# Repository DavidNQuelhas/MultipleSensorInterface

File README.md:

# MultipleSensorInterface
Multiple Sensor Interface - versatile RTU device

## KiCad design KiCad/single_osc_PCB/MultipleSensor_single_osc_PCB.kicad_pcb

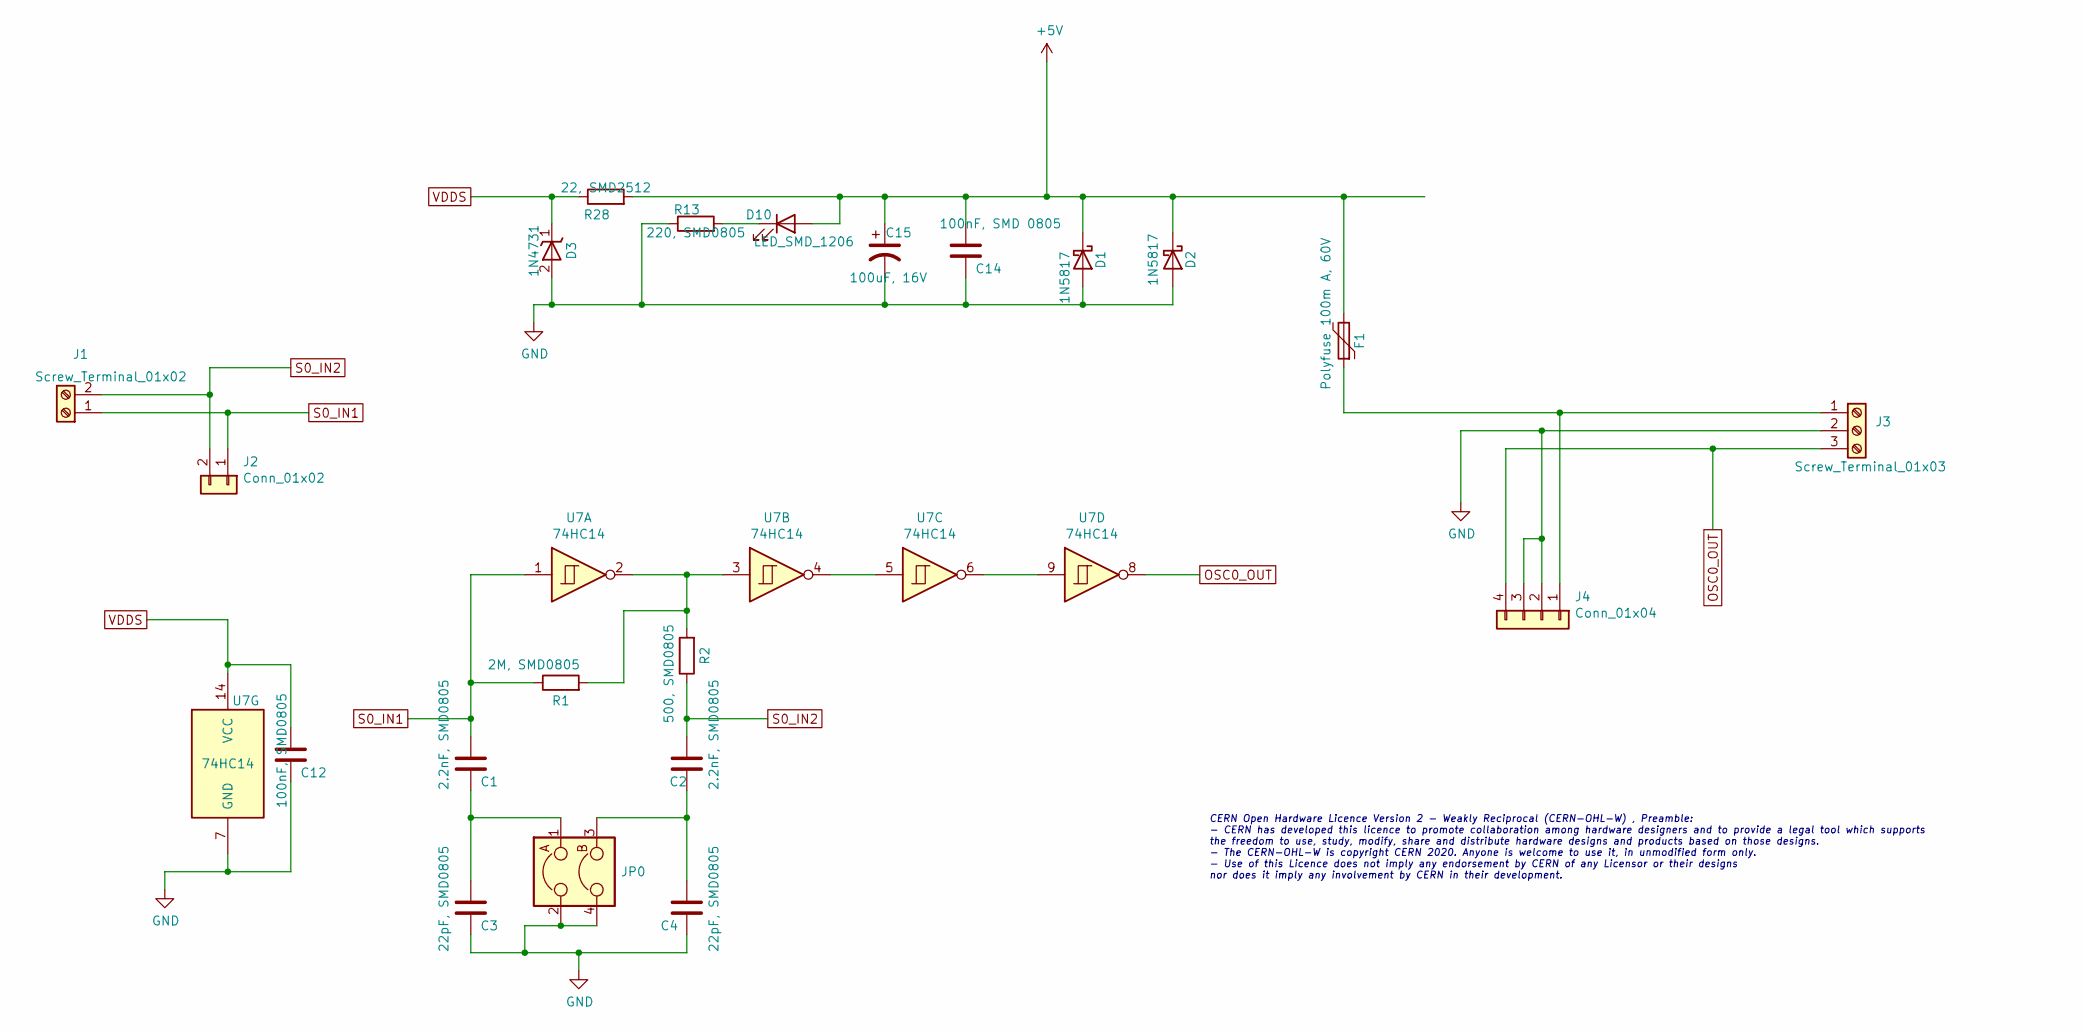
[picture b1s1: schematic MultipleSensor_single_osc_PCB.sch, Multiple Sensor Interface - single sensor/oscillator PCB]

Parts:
C1, C2: 2.2nF, SMD0805; C_0805_HandSoldering
C3, C4: 22pF, SMD0805; C_0805_HandSoldering
C12: 100nF, SMD0805; C_0805_HandSoldering
C14: 100nF, SMD 0805; C_0805_HandSoldering
C15: 100uF, 16V; CP_Radial_D5.0mm_P2.50mm
D1, D2: 1N5817; D_DO-41_SOD81_P10.16mm_Horizontal
D3: 1N4731; D_DO-41_SOD81_P10.16mm_Horizontal
D10: LED_SMD_1206; LED_1206
F1: Polyfuse 100m A, 60V; Fuse_TE5_Littlefuse-395Series
J1: Screw_Terminal_01x02; TerminalBlock_Screw_1x2_3.96mm
J2: Conn_01x02; PinHeader_1x02_P2.54mm_Vertical_HandSoldering
J3: Screw_Terminal_01x03; TerminalBlock_Screw_1x3_3.96mm
J4: Conn_01x04; PinHeader_1x04_P2.54mm_Vertical_HandSoldering
JP0: 2_jumpers_related; 2_jumpers_related_2.54mm
R1: 2M, SMD0805; R_0805_HandSoldering
R2: 500, SMD0805; R_0805_HandSoldering
R13: 220, SMD0805; R_0805_HandSoldering
R28: 22, SMD2512; R_2512_HandSoldering
U7: 74HC14; SOIC-14_3.9x8.7mm_Pitch1.27mm_HandSoldering

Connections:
+5V: C14.1, C15.1, D1.1 (K), D2.1 (K), D10.2 (A), F1.2, R28.2
GND: C3.2, C4.2, C12.2, C14.2, C15.2, D1.2 (A), D2.2 (A), D3.2 (A), J3.2, J4.2, J4.3, JP0.2, JP0.4, R13.1, U7.7 (GND)
unnamed: C1.2, C3.1, JP0.1
unnamed: C2.2, C4.1, JP0.3
unnamed: D10.1 (K), R13.2
unnamed: F1.1, J3.1, J4.1
unnamed: R1.2, R2.2, U7.2, U7.3
unnamed: U7.4, U7.5
unnamed: U7.6, U7.9
OSC0_OUT: J3.3, J4.4, U7.8
S0_IN1: C1.1, J1.1, J2.1, R1.1, U7.1
S0_IN2: C2.1, J1.2, J2.2, R2.1
VDDS: C12.1, D3.1 (K), R28.1, U7.14 (VCC)

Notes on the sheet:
CERN Open Hardware Licence Version 2 - Weakly Reciprocal (CERN-OHL-W) , Preamble: - CERN has developed this licence to promote collaboration among hardware designers and to provide a legal tool which supports the freedom to use, study, modify, share and distribute hardware designs and products base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

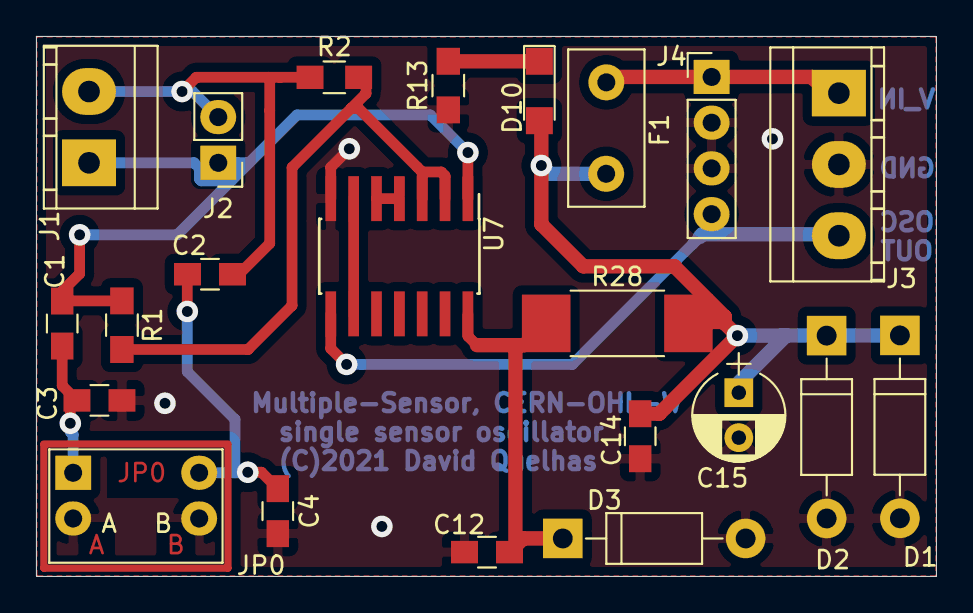
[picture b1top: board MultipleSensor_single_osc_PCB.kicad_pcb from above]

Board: 2 copper layers, 50.0 x 30.0 mm, 22 parts (0 on the bottom side), 13 nets.

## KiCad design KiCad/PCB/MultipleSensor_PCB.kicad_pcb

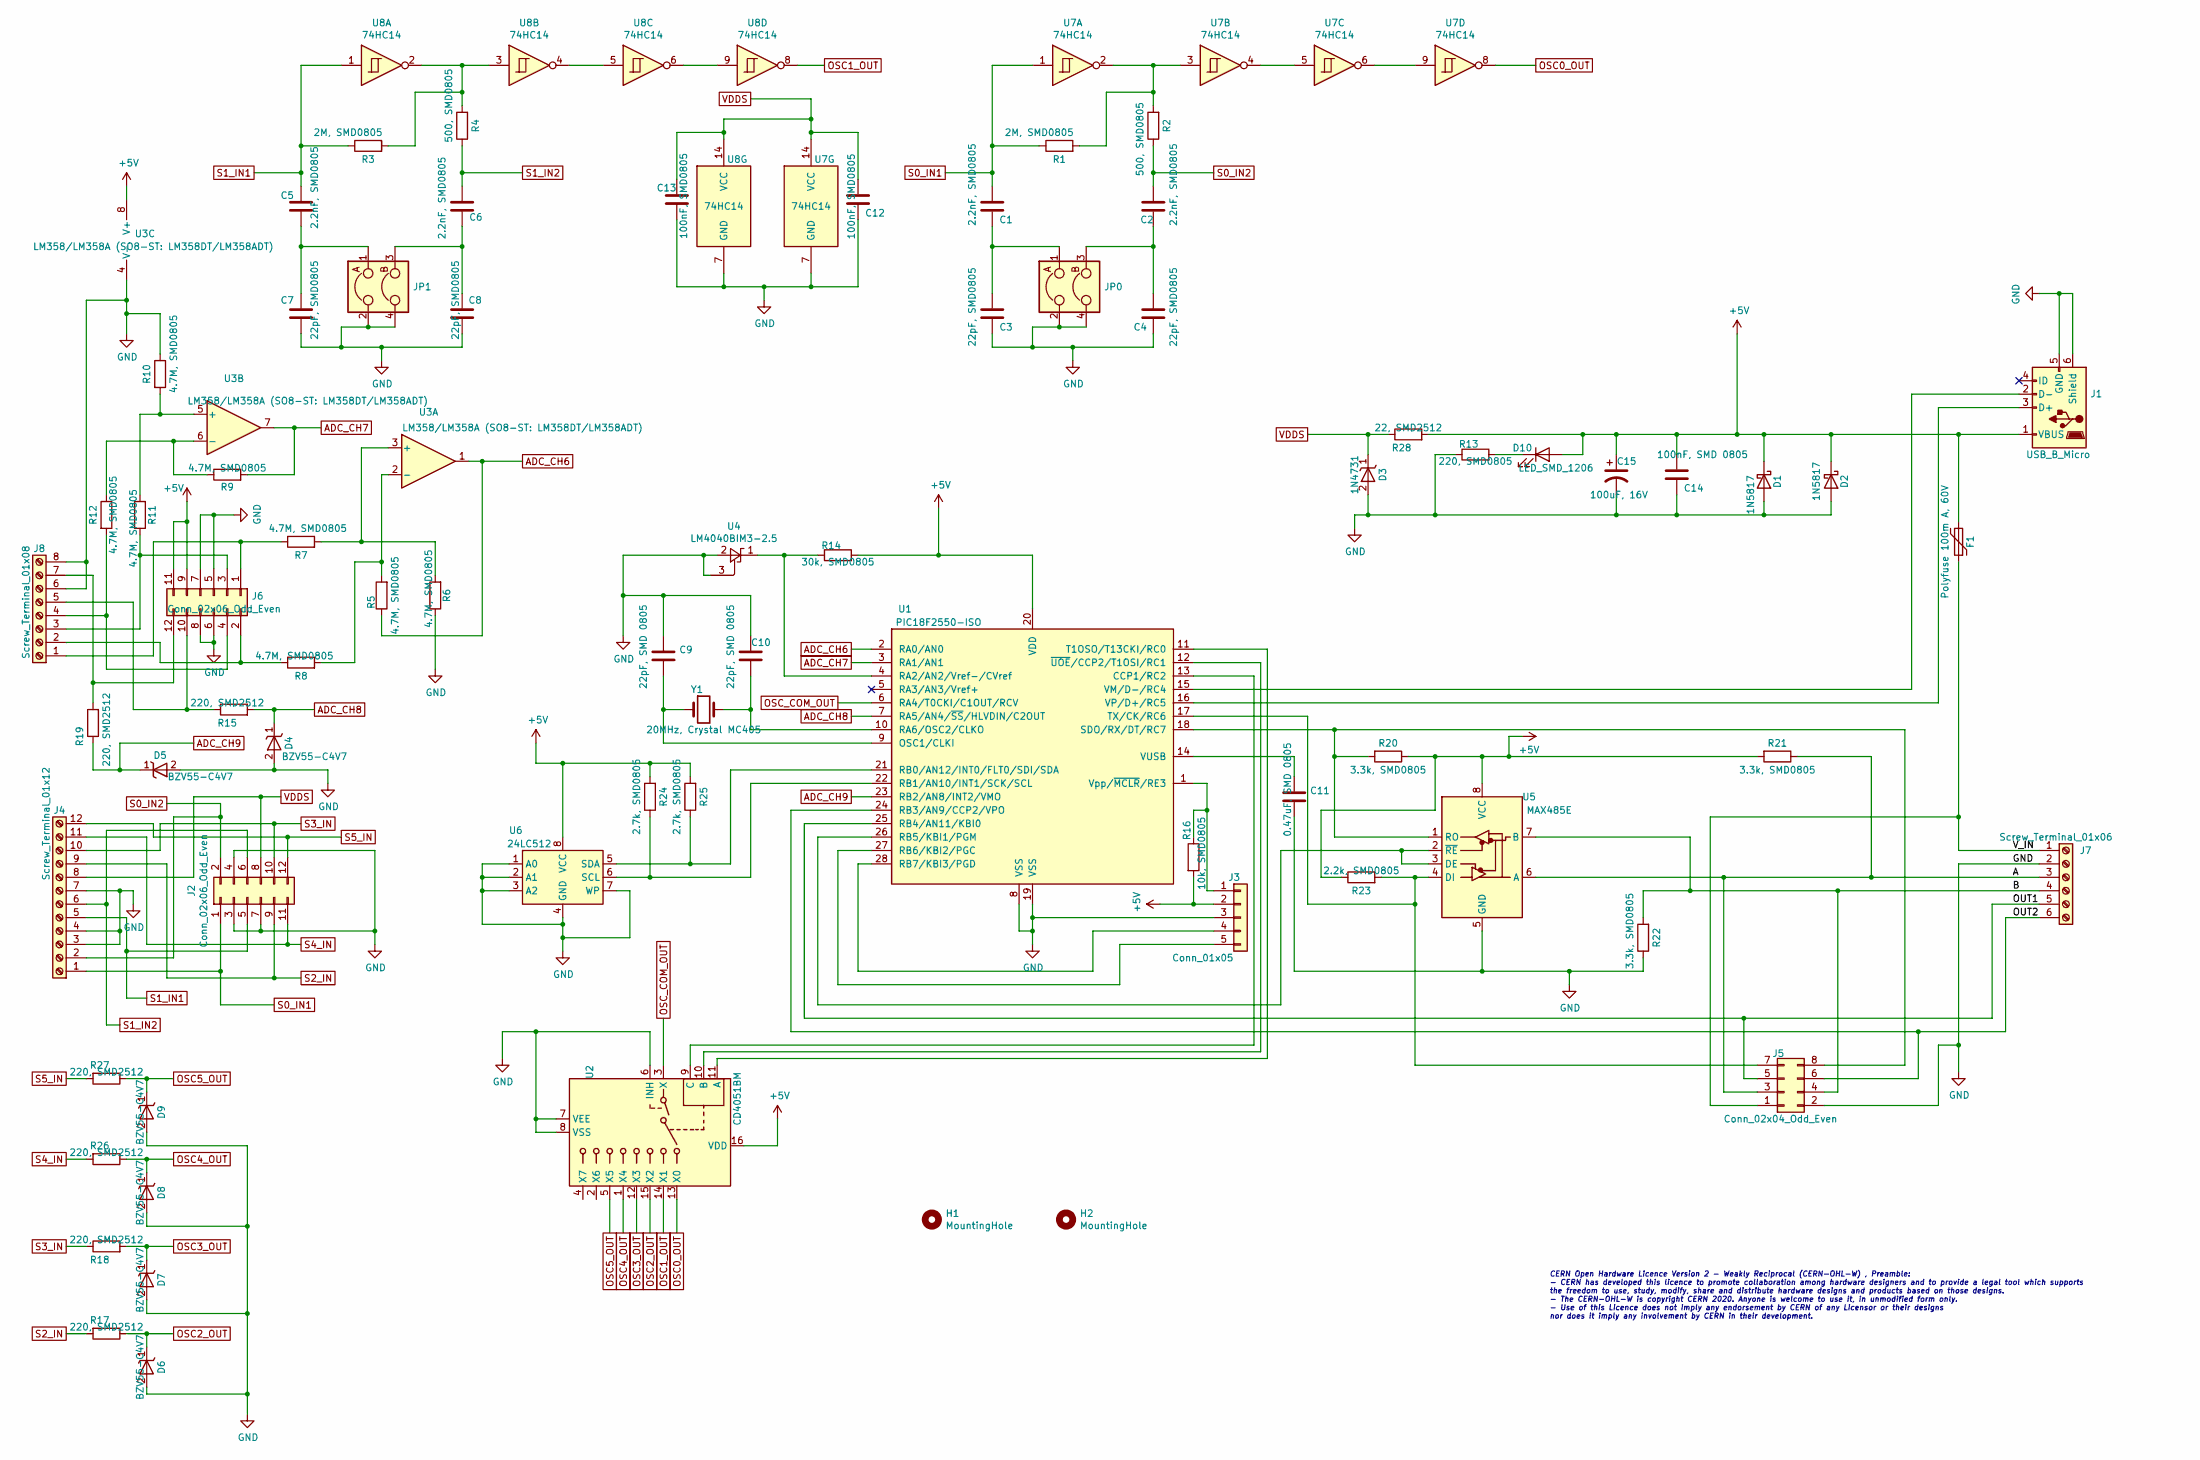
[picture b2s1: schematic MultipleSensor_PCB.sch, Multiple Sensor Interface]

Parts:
C1, C2, C5, C6: 2.2nF, SMD0805; C_0805_HandSoldering
C3, C4, C7, C8: 22pF, SMD0805; C_0805_HandSoldering
C9, C10: 22pF, SMD 0805; C_0805_HandSoldering
C11: 0.47uF, SMD 0805; C_0805_HandSoldering
C12, C13: 100nF, SMD0805; C_0805_HandSoldering
C14: 100nF, SMD 0805; C_0805_HandSoldering
C15: 100uF, 16V; CP_Radial_D5.0mm_P2.50mm
D1, D2: 1N5817; D_DO-41_SOD81_P10.16mm_Horizontal
D3: 1N4731; D_DO-41_SOD81_P10.16mm_Horizontal
D4, D5, D6, D7, D8, D9: BZV55-C4V7; D_1206
D10: LED_SMD_1206; LED_1206
F1: Polyfuse 100m A, 60V; Fuse_TE5_Littlefuse-395Series
H1, H2: MountingHole; MountingHole_3.2mm_M3_Pad
J1: USB_B_Micro; USB_mini_B_HandSoldering
J2, J6: Conn_02x06_Odd_Even; PinHeader_2x06_P2.54mm_Vertical_HandSoldering
J3: Conn_01x05; PinHeader_1x05_P2.54mm_Vertical_HandSoldering
J4: Screw_Terminal_01x12; TerminalBlock_Screw_1x12_3.96mm
J5: Conn_02x04_Odd_Even; PinHeader_2x04_P2.54mm_Vertical_HandSoldering
J7: Screw_Terminal_01x06; TerminalBlock_Screw_1x6_3.96mm
J8: Screw_Terminal_01x08; TerminalBlock_Screw_1x8_3.96mm_mirror
JP0, JP1: 2_jumpers_related; 2_jumpers_related_2.54mm
R1, R3: 2M, SMD0805; R_0805_HandSoldering
R2, R4: 500, SMD0805; R_0805_HandSoldering
R5, R6, R7, R8, R9, R10, R11, R12: 4.7M, SMD0805; R_0805_HandSoldering
R13: 220, SMD0805; R_0805_HandSoldering
R14: 30k, SMD0805; R_0805_HandSoldering
R15, R17, R18, R19, R26, R27: 220, SMD2512; R_2512_HandSoldering
R16: 10k, SMD0805; R_0805_HandSoldering
R20, R21, R22: 3.3k, SMD0805; R_0805_HandSoldering
R23: 2.2k, SMD0805; R_0805_HandSoldering
R24, R25: 2.7k, SMD0805; R_0805_HandSoldering
R28: 22, SMD2512; R_2512_HandSoldering
U1: PIC18F2550-ISO; SOIC-28W_7.5x17.9mm_P1.27mm_HandSoldering
U2: CD4051BM; SOIC-16_3.9x9.9mm_Pitch1.27mm_HandSoldering
U3: LM358/LM358A (SO8-ST: LM358DT/LM358ADT); SOIC-8_3.9x4.9mm_Pitch1.27mm_HandSoldering
U4: LM4040BIM3-2.5; SOT-23_HandSoldering2
U5: MAX485E; SOIC-8_3.9x4.9mm_Pitch1.27mm_HandSoldering
U6: 24LC512; SOIC-8_3.9x4.9mm_Pitch1.27mm_HandSoldering
U7, U8: 74HC14; SOIC-14_3.9x8.7mm_Pitch1.27mm_HandSoldering
Y1: 20MHz, Crystal MC405; Crystal_SMD_MC405-2pin_9.6mmx4.1mm_HandSoldering

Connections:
+5V: C14.1, C15.1, D1.1 (K), D2.1 (K), D10.2 (A), F1.2, J1.1 (VBUS), J3.2, J6.9, J6.11, R14.2, R16.2, R20.1, R21.2, R23.1, R24.2, R25.2, R28.2, U1.20 (VDD), U2.16 (VDD), U3.8 (V+), U5.8 (VCC), U6.8 (VCC)
/A: J5.3, J7.3, R21.1, U5.6 (A)
/B: J5.4, J7.4, R22.2, U5.7 (B)
/OUT1: J5.5, J7.5, U1.25 (RB4/AN11/KBI0)
/OUT2: J5.6, J7.6, U1.24 (RB3/AN9/CCP2/VPO)
/V_IN: F1.1, J5.1, J7.1
ADC_CH6: R5.1, U1.2 (RA0/AN0), U3.1
ADC_CH7: R9.2, U1.3 (RA1/AN1), U3.7
ADC_CH8: D4.1 (K), R15.2, U1.7 (RA5/AN4/~SS~/HLVDIN/C2OUT)
ADC_CH9: D5.1 (K), R19.1, U1.23 (RB2/AN8/INT2/VMO)
GND: C3.2, C4.2, C7.1, C8.1, C9.1, C10.1, C11.2, C12.2, C13.1, C14.2, C15.2, D1.2 (A), D2.2 (A), D3.2 (A), D4.2 (A), D5.2 (A), D6.2 (A), D7.2 (A), D8.2 (A), D9.2 (A), J1.5 (GND), J1.6 (Shield), J2.3, J2.4, J2.7, J3.3, J4.3, J4.4, J4.7, J5.2, J6.5, J6.6, J6.7, J6.8, J7.2, J8.6, J8.8, JP0.2, JP0.4, JP1.2, JP1.4, R6.1, R10.1, R13.1, R22.1, U1.8 (VSS), U1.19 (VSS), U2.6 (INH), U2.7 (VEE), U2.8 (VSS), U3.4 (V-), U4.2 (A), U4.3 (B), U5.5 (GND), U6.1 (A0), U6.2 (A1), U6.3 (A2), U6.4 (GND), U6.7 (WP), U7.7 (GND), U8.7 (GND)
unnamed: C1.2, C3.1, JP0.1
unnamed: C2.2, C4.1, JP0.3
unnamed: C5.1, C7.2, JP1.1
unnamed: C6.2, C8.2, JP1.3
unnamed: C9.2, U1.9 (OSC1/CLKI), Y1.1
unnamed: C10.2, U1.10 (RA6/OSC2/CLKO), Y1.2
unnamed: C11.1, U1.14 (VUSB)
unnamed: D10.1 (K), R13.2
unnamed: J1.2 (D-), U1.15 (VM/D-/RC4)
unnamed: J1.3 (D+), U1.16 (VP/D+/RC5)
unnamed: J3.1, R16.1, U1.1 (Vpp/~MCLR~/RE3)
unnamed: J3.4, U1.28 (RB7/KBI3/PGD)
unnamed: J3.5, U1.27 (RB6/KBI2/PGC)
unnamed: J5.7, R23.2, U1.17 (TX/CK/RC6), U5.4 (DI)
unnamed: J5.8, R20.2, U1.18 (SDO/RX/DT/RC7), U5.1 (RO)
unnamed: J6.1, J8.1, R7.1
unnamed: J6.2, J8.2, R8.1
unnamed: J6.3, J8.3, R11.1
unnamed: J6.4, J8.4, R12.2
unnamed: J6.10, J8.5, R15.1
unnamed: J6.12, J8.7, R19.2
unnamed: R1.2, R2.2, U7.2, U7.3
unnamed: R3.2, R4.2, U8.2, U8.3
unnamed: R5.2, R8.2, U3.2 (-)
unnamed: R6.2, R7.2, U3.3 (+)
unnamed: R10.2, R11.2, U3.5 (+)
unnamed: R9.1, R12.1, U3.6 (-)
unnamed: R14.1, U1.4 (RA2/AN2/Vref-/CVref), U4.1 (K)
unnamed: R24.1, U1.22 (RB1/AN10/INT1/SCK/SCL), U6.6 (SCL)
unnamed: R25.1, U1.21 (RB0/AN12/INT0/FLT0/SDI/SDA), U6.5 (SDA)
unnamed: U1.11 (T1OSO/T13CKI/RC0), U2.11 (A)
unnamed: U1.12 (~UOE~/CCP2/T1OSI/RC1), U2.10 (B)
unnamed: U1.13 (CCP1/RC2), U2.9 (C)
unnamed: U1.26 (RB5/KBI1/PGM), U5.2 (~RE), U5.3 (DE)
unnamed: U7.4, U7.5
unnamed: U7.6, U7.9
unnamed: U8.4, U8.5
unnamed: U8.6, U8.9
OSC0_OUT: U2.13 (X0), U7.8
OSC1_OUT: U2.14 (X1), U8.8
OSC2_OUT: D6.1 (K), R17.1, U2.15 (X2)
OSC3_OUT: D7.1 (K), R18.2, U2.12 (X3)
OSC4_OUT: D8.1 (K), R26.1, U2.1 (X4)
OSC5_OUT: D9.1 (K), R27.1, U2.5 (X5)
OSC_COM_OUT: U1.6 (RA4/T0CKI/C1OUT/RCV), U2.3 (X)
S0_IN1: C1.1, J2.1, J4.1, R1.1, U7.1
S0_IN2: C2.1, J2.2, J4.2, R2.1
S1_IN1: C5.2, J2.5, J4.5, R3.1, U8.1
S1_IN2: C6.1, J2.6, J4.6, R4.1
S2_IN: J2.9, J4.9, R17.2
S3_IN: J2.10, J4.10, R18.1
S4_IN: J2.11, J4.11, R26.2
S5_IN: J2.12, J4.12, R27.2
VDDS: C12.1, C13.2, D3.1 (K), J2.8, J4.8, R28.1, U7.14 (VCC), U8.14 (VCC)

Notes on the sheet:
CERN Open Hardware Licence Version 2 - Weakly Reciprocal (CERN-OHL-W) , Preamble: - CERN has developed this licence to promote collaboration among hardware designers and to provide a legal tool which supports the freedom to use, study, modify, share and distribute hardware designs and products base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

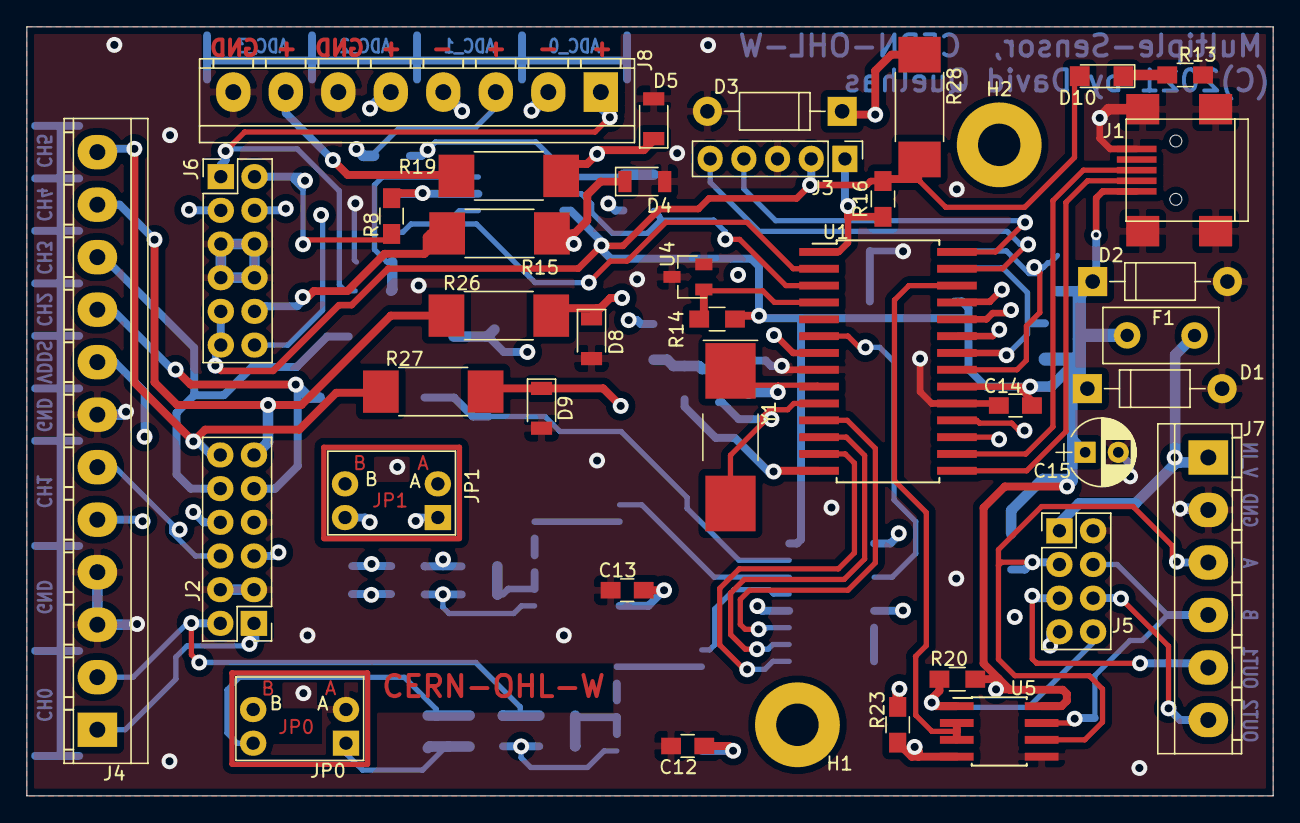
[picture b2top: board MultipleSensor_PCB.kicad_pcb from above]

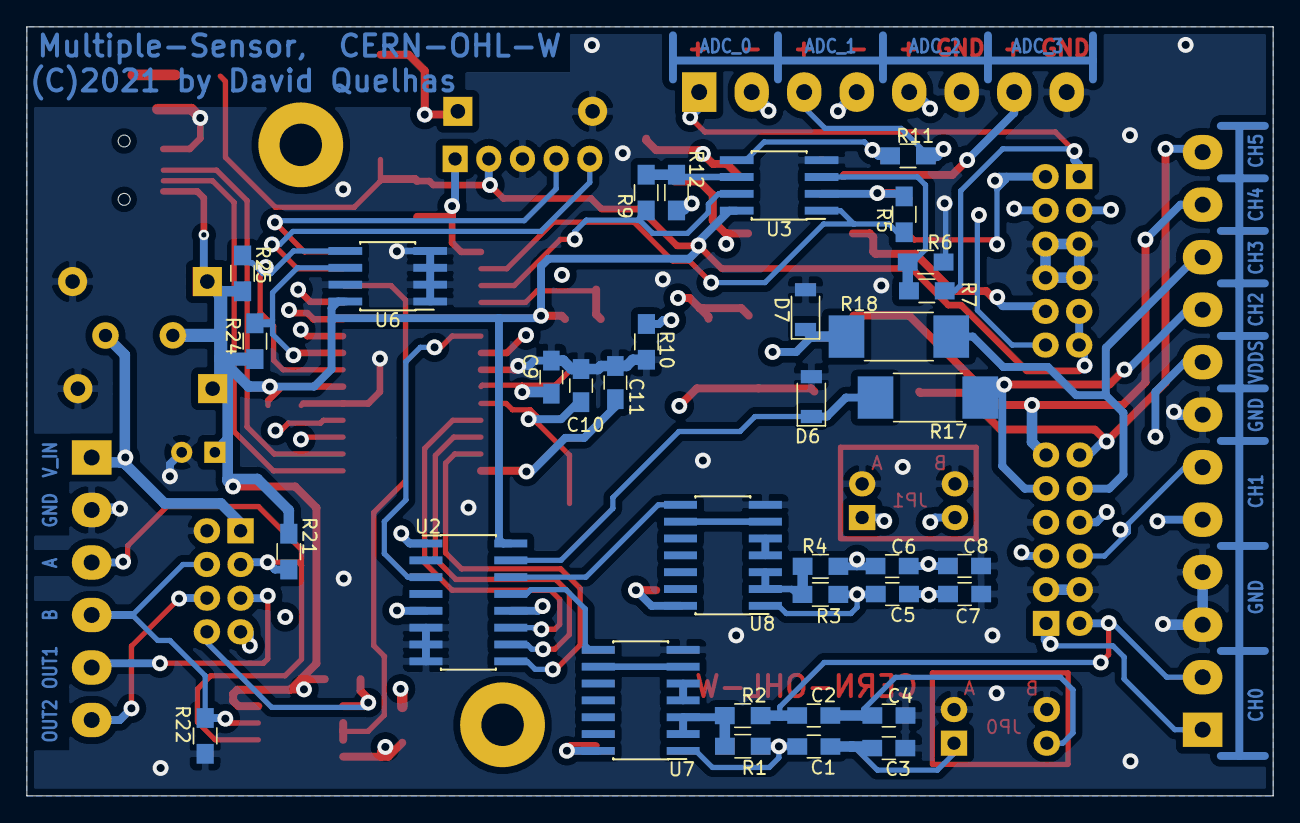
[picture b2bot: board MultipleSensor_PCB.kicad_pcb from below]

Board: 4 copper layers, 94.0 x 58.0 mm, 75 parts (35 on the bottom side), 65 nets.

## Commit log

2021-09-19 Multiple Sensor Interface project initial commit

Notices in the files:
KiCad/PCB/MultipleSensor_PCB.kicad_pcb:
Multiple-Sensor,  CERN-OHL-W
(C)2021 by David Quelhas
KiCad/PCB/MultipleSensor_PCB.sch:
David N. G. da Silva S. Quelhas (Lisboa - Portugal)  ,  License: CERN-OHL-W
- The CERN-OHL-W is copyright CERN 2020. Anyone is welcome to use it, in unmodified form only.
KiCad/single_osc_PCB/MultipleSensor_single_osc_PCB.kicad_pcb:
(C)2021 David Quelhas
